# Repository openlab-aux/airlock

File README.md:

# Airlock

This repository contains various soft- and hardware sources for the OpenLab Augsburg Airlock.

## zvezda

Zvezda is the temporary solution for Airlock. See (Zvezda)[zvezda/README.md].

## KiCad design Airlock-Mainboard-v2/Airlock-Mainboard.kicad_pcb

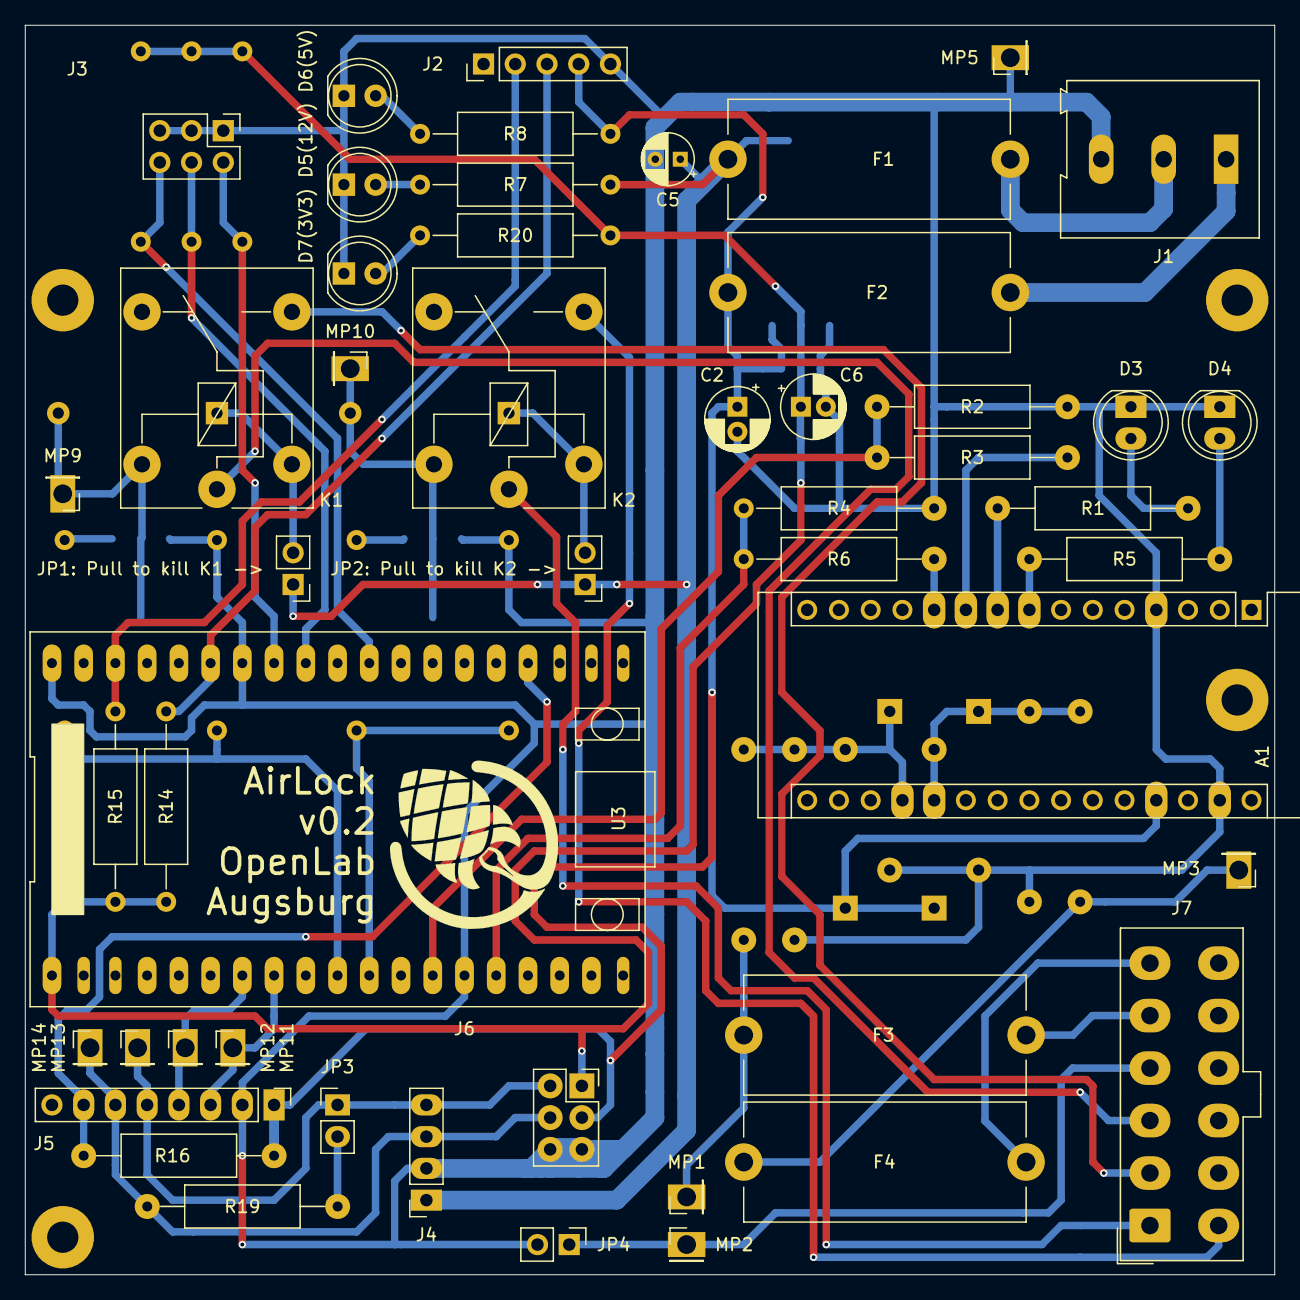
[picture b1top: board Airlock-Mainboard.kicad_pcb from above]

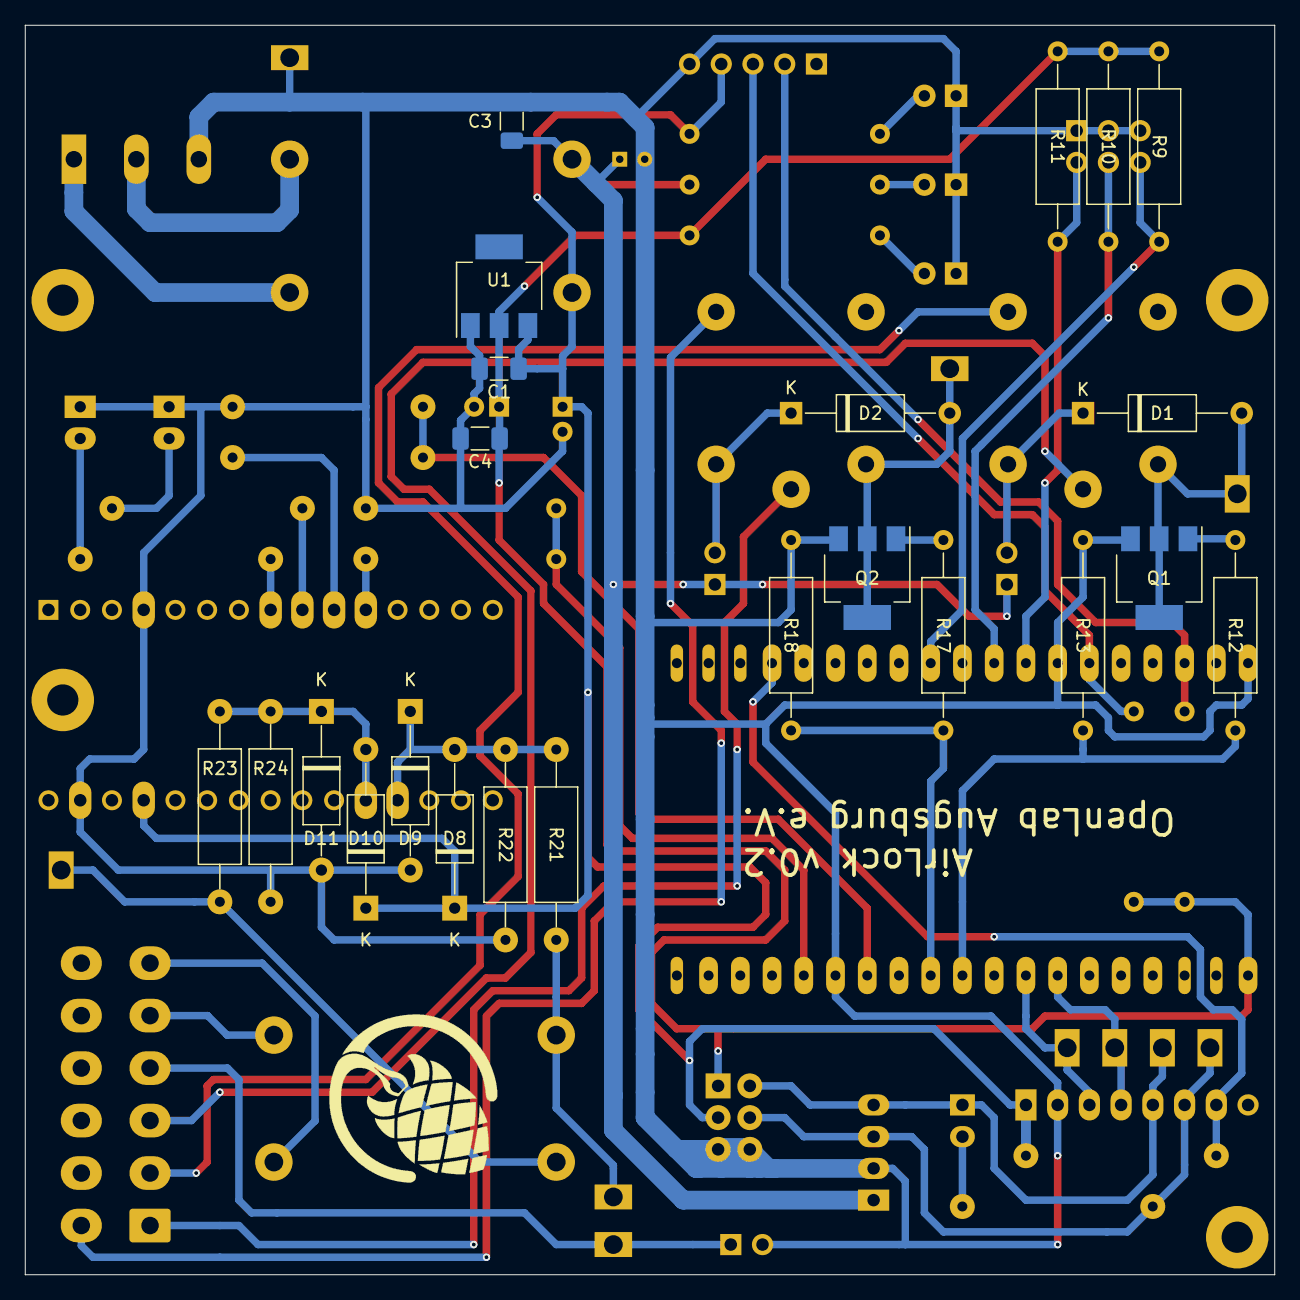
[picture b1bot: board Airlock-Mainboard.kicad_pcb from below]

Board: 2 copper layers, 100.0 x 100.0 mm, 73 parts (23 on the bottom side), 47 nets.

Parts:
A1: Arduino_Nano_v3.x; Arduino_Nano
C1, C3, C4: 100n; C_1206_3216Metric_Pad1.33x1.80mm_HandSolder
C2, C6: 10u; CP_Radial_D5.0mm_P2.00mm
C5: 10u; CP_Radial_D4.0mm_P2.00mm
D1, D2, D8, D9, D10, D11: BAT41; D_A-405_P12.70mm_Horizontal
D3: (Inn) rd 2mA; LED_D5.0mm
D4: (Auß) rd 2mA; LED_D5.0mm
D5(12V), D6(5V), D7(3V3): rd 2mA; LED_D5.0mm
F1, F2, F3, F4: Fuse; Fuseholder_Cylinder-5x20mm_Stelvio-Kontek_PTF78_Horizontal_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
J1: Screw_Terminal_01x03; TerminalBlock_Altech_AK300-3_P5.00mm
J2: Conn_01x05_LCD; PinHeader_1x05_P2.54mm_Vertical
J3: Conn_02x03_Taster; PinHeader_2x03_P2.54mm_Vertical
J4: Conn_01x04; PinSocket_1x04_P2.54mm_Vertical
J5: TJA1051 BO Board (MCP2552I); PinHeader_1x08_P2.54mm_Vertical
J6: Conn_02x03_Odd_Even; PinSocket_2x03_P2.54mm_Vertical
J7: Conn_02x06_Top_Bottom; Molex_Mini-Fit_Jr_5566-12A_2x06_P4.20mm_Vertical
JP1: Pull to kill K1 ->, JP2: Pull to kill K2 ->: Kill-Jumper; PinHeader_1x02_P2.54mm_Vertical
JP3: Jumper_2_Open; PinHeader_1x02_P2.54mm_Vertical
JP4: KACGND-Jumper; PinHeader_1x02_P2.54mm_Vertical
K1, K2: FINDER-36.11; Relay_SPDT_Finder_36.11
MP1, MP2, MP3, MP5, MP9, MP10, MP11, MP12, MP13, MP14: Messpunkt; PinHeader_1x01_P2.54mm_Vertical
Q1, Q2: BSP89; SOT-223-3_TabPin2
R1, R5, R8: 1k5; R_Axial_DIN0309_L9.0mm_D3.2mm_P15.24mm_Horizontal
R2, R3, R4, R6: ?; R_Axial_DIN0309_L9.0mm_D3.2mm_P15.24mm_Horizontal
R7, R9, R10, R11, R14, R15: 4k7; R_Axial_DIN0309_L9.0mm_D3.2mm_P15.24mm_Horizontal
R12, R17: 47; R_Axial_DIN0309_L9.0mm_D3.2mm_P15.24mm_Horizontal
R13, R18: 100k; R_Axial_DIN0309_L9.0mm_D3.2mm_P15.24mm_Horizontal
R16: 47k; R_Axial_DIN0309_L9.0mm_D3.2mm_P15.24mm_Horizontal
R19: 120; R_Axial_DIN0309_L9.0mm_D3.2mm_P15.24mm_Horizontal
R20: 680; R_Axial_DIN0309_L9.0mm_D3.2mm_P15.24mm_Horizontal
R21, R23: 6k8; R_Axial_DIN0309_L9.0mm_D3.2mm_P15.24mm_Horizontal
R22, R24: 2k2; R_Axial_DIN0309_L9.0mm_D3.2mm_P15.24mm_Horizontal
U1: LM1117-3.3; SOT-223
U3: ESP32-WROOM-32; AZ-Delivery_ESP32Wroom32_withUSB_module

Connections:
+3V3: C4.1, C6.1, J6.1, R9.2, R10.2, R11.2, R14.2, R15.2, R20.2, U1.2, U3.2
+5V: A1.27, C1.1, C2.1, D8.1, D10.1, F2.1, J2.4, J5.1, J6.3, R8.2, R16.1, U1.3
+12V: C3.1, C5.1, F1.2, J4.1, JP1: Pull to kill K1 ->.1, JP2: Pull to kill K2 ->.1, R7.2
BuzzerAussen_3V3: R12.2, R13.2, U3.11
BuzzerInnen_3V3: R17.2, R18.2, U3.12
Buzzer_Aussen_AC1: J7.2, K1.14
Buzzer_Aussen_AC2: J7.3, K1.11
Buzzer_Innen_AC1: J7.7, K2.14
Buzzer_Innen_AC2: J7.1, K2.11
CAN_HIGH: J4.4, J5.5, J6.2, JP3.1, MP13.1
CAN_LOW: J4.3, J5.6, J6.4, MP14.1, R19.2
CAN_RX: J5.4, MP12.1, U3.8
CAN_TX: J5.3, MP11.1, U3.9
GND: A1.3, A1.29, C1.2, C2.2, C3.2, C4.2, C5.2, C6.2, D3.1, D4.1, D5(12V).1, D6(5V).1, D7(3V3).1, D9.2, D11.2, J1.3, J2.5, J3.1, J3.3, J3.5, J4.2, J5.2, J6.5, J6.6, JP4.2, MP5.1, Q1.3, Q2.3, R2.2, R4.2, R13.1, R18.1, R22.2, R24.2, U1.1, U3.1
I2C_SCL: J2.2, R15.1, U3.36
I2C_SDA: J2.3, R14.1, U3.33
KlingelAussen_3V3: R2.1, R3.1, U3.14
KlingelInnen_3V3: R4.1, R6.2, U3.16
Klingel_AC_GND: J7.4, JP4.1, MP2.1
Klingel_Aussen_AC_in: F3.2, J7.5
Klingel_Innen_AC_in: F4.2, J7.6
unnamed: A1.8, R5.2
unnamed: A1.9, R1.2
unnamed: A1.10, R3.2
unnamed: A1.11, R6.1
unnamed: A1.19, D8.2, D9.1, R21.2, R22.1
unnamed: A1.20, D10.2, D11.1, R23.2, R24.1
unnamed: D1.1, JP1: Pull to kill K1 ->.2, K1.A1
unnamed: D1.2, K1.A2, MP9.1, Q1.2
unnamed: D2.1, JP2: Pull to kill K2 ->.2, K2.A1
unnamed: D2.2, K2.A2, MP10.1, Q2.2
unnamed: D3.2, R1.1
unnamed: D4.2, R5.1
unnamed: D5(12V).2, R7.1
unnamed: D6(5V).2, R8.1
unnamed: D7(3V3).2, R20.1
unnamed: F1.1, J1.2
unnamed: F2.2, J1.1
unnamed: F3.1, MP1.1, R21.1
unnamed: F4.1, MP3.1, R23.1
unnamed: JP3.2, R19.1
unnamed: Q1.1, R12.1
unnamed: Q2.1, R17.1
TJA1051_S: J5.7, R16.2, U3.23
Taster_A1: J3.6, R9.1, U3.28
Taster_B1: J3.4, R10.1, U3.30
Taster_C1: J3.2, R11.1, U3.31

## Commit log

2022-05-02 zvezda: add initial implementation
2022-05-03 Add README.md
2022-05-03 feat(zvezda): add developer mode
2022-05-03 feat(zvezda): improve cooldown
2022-05-03 chore(zvezda): improved logging
2022-05-03 fix(zvezda): enable pin code
2022-05-03 fix(zvezda): fix embedded files
2022-07-10 feat: improve error handling in the user interface
2022-07-10 feat: update user
2022-07-10 feat: add delete feature
2023-09-24 added Mainboard v2 Files
